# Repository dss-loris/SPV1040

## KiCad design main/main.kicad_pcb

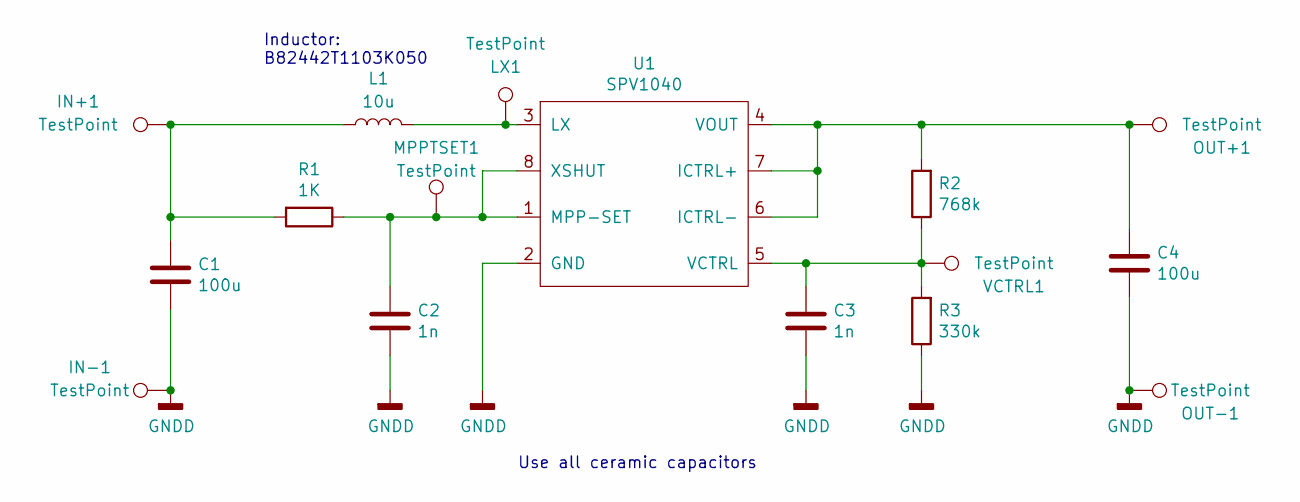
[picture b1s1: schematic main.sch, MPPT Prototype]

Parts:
C1, C4: 100u; C_1206_3216Metric_Pad1.42x1.75mm_HandSolder
C2, C3: 1n; C_1206_3216Metric_Pad1.42x1.75mm_HandSolder
IN+1: TestPoint; PinHeader_1x01_P2.54mm_Vertical
IN-1: TestPoint; PinHeader_1x01_P2.54mm_Vertical
L1: 10u; B82442T1103K050
LX1: TestPoint; PinHeader_1x01_P2.54mm_Vertical
MPPTSET1: TestPoint; PinHeader_1x01_P2.54mm_Vertical
OUT+1: TestPoint; PinHeader_1x01_P2.54mm_Vertical
OUT-1: TestPoint; PinHeader_1x01_P2.54mm_Vertical
R1: 1K; R_1206_3216Metric_Pad1.42x1.75mm_HandSolder
R2: 768k; R_1206_3216Metric_Pad1.42x1.75mm_HandSolder
R3: 330k; R_1206_3216Metric_Pad1.42x1.75mm_HandSolder
U1: SPV1040; TSSOP-8_4.4x3mm_P0.65mm
VCTRL1: TestPoint; PinHeader_1x01_P2.54mm_Vertical

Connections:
GNDD: C1.2, C2.2, C3.2, C4.2, IN-1.1, OUT-1.1, R3.1, U1.2 (GND)
unnamed: C1.1, IN+1.1, L1.1, R1.2
unnamed: C2.1, MPPTSET1.1, R1.1, U1.1 (MPP-SET), U1.8 (XSHUT)
unnamed: C3.1, R2.1, R3.2, U1.5 (VCTRL), VCTRL1.1
unnamed: C4.1, OUT+1.1, R2.2, U1.4 (VOUT), U1.6 (ICTRL-), U1.7 (ICTRL+)
unnamed: L1.2, LX1.1, U1.3 (LX)

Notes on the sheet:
Inductor: B82442T1103K050
Use all ceramic capacitors

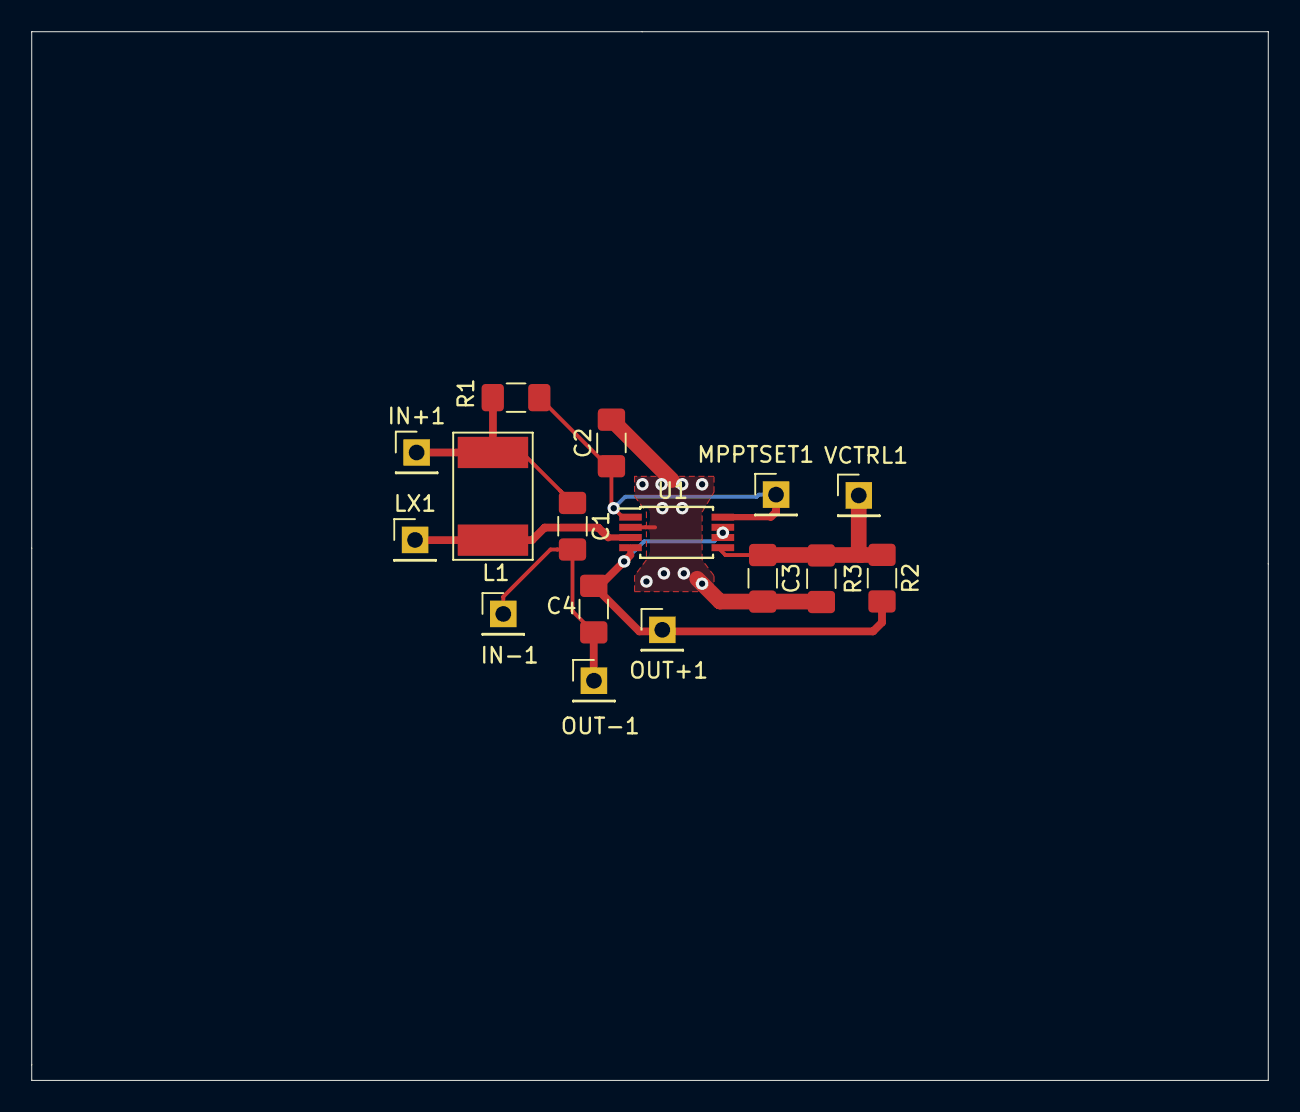
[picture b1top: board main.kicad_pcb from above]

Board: 2 copper layers, 79.0 x 67.0 mm, 16 parts (0 on the bottom side), 6 nets.

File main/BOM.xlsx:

Id;"Designator";"Package";"Quantity";"Designation";"Supplier and ref";
1;"U1";"TSSOP-8_4.4x3mm_P0.65mm";1;"SPV1040";;;
2;"C1 | C4";"C_1206_3216Metric_Pad1.42x1.75mm_HandSolder";2;"100u";;;
3;"C2 | C3";"C_1206_3216Metric_Pad1.42x1.75mm_HandSolder";2;"1n";;;
4;"IN+1 | IN-1 | LX1 | MPPTSET1 | OUT+1 | OUT-1 | VCTRL1";"PinHeader_1x01_P2.54mm_Vertical";7;"TestPoint";;;
5;"L1";"B82442T1103K050";1;"10u";;;
6;"R1";"R_1206_3216Metric_Pad1.42x1.75mm_HandSolder";1;"1K";;;
7;"R2";"R_1206_3216Metric_Pad1.42x1.75mm_HandSolder";1;"768k";;;
8;"R3";"R_1206_3216Metric_Pad1.42x1.75mm_HandSolder";1;"330k";;;

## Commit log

2019-12-18 picked_footprints
2019-12-18 progress
2020-01-07 gerber
2020-01-28 addded_bom
2021-03-10 added_pdf
